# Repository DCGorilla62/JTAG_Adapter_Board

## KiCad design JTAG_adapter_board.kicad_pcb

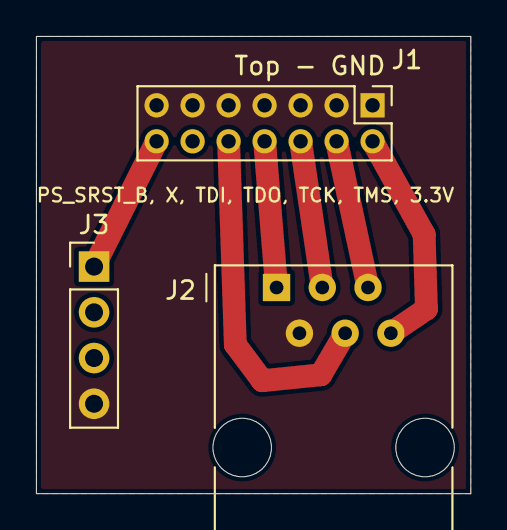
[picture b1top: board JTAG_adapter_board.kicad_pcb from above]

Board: 2 copper layers, 24.1 x 25.4 mm, 3 parts (0 on the bottom side), 7 nets.

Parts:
J1: JTAG conn; PinHeader_2x07_P2.00mm_Vertical
J2: RJ11; RJ12_Amphenol_54601
J3: P_SRST_breakout; PinHeader_1x04_P2.54mm_Vertical

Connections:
+3V3: J1.14, J2.6
/PS_SRST_B: J1.8, J3.1
/TCK: J1.12, J2.3
/TD0: J1.11, J2.1
/TDI: J1.10, J2.4
/TMS: J1.13, J2.5
GND: J1.1, J1.2, J1.3, J1.4, J1.5, J1.6, J1.7, J2.2, J3.4

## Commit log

2022-12-20 JTAG adapter board from long long ago
2022-12-22 Ground plane
2022-12-22 Edits from keith, ready for fab
